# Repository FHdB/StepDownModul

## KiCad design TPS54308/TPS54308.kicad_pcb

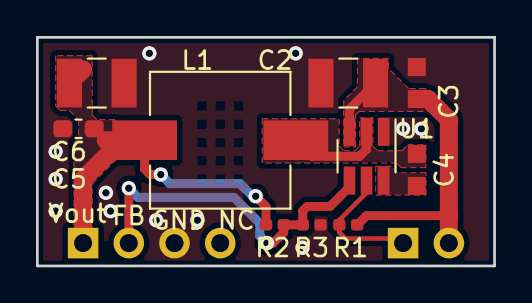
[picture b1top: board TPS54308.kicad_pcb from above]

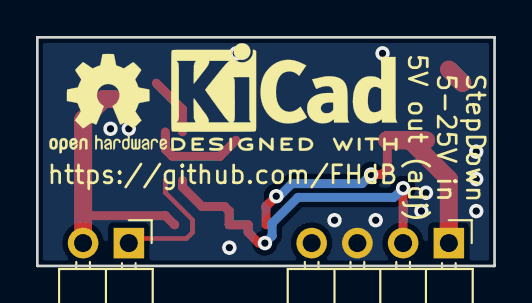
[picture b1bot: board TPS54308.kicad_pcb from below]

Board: 2 copper layers, 25.4 x 12.7 mm, 12 parts (2 on the bottom side), 7 nets.

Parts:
C2: 10u/50V/1210; C_1210_3225Metric_Pad1.39x2.70mm_HandSolder
C3, C4: 100n/50V/0603; C_0603_1608Metric_Pad0.99x1.00mm_HandSolder
C5: 100n/6.3V/0402; C_0603_1608Metric_Pad1.05x0.95mm_HandSolder
C6: 22u/6.3V/1210; C_1210_3225Metric_Pad1.39x2.70mm_HandSolder
L1: 74437346082_8u2_3.25A; L_Wuerth_WE-PD-Typ-M-Typ-S_Handsoldering
P1: CONN_01X02; PinHeader_1x02_P2.54mm_Horizontal
P2: CONN_01X04; PinHeader_1x04_P2.54mm_Horizontal
R1, R2: 100k/0402; R_0402_1005Metric_Handsolder
R3: 22k/0402; R_0402_1005Metric_Handsolder
U1: TPS54308DDC; SOT-23-6_Handsoldering

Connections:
BOOT: C4.1, U1.6
EN: P1.1, R1.2, U1.5
FB: P2.2, R2.2, R3.1, U1.4
GND: C2.2, C3.2, C5.2, C6.2, P2.3, R3.2, U1.1
SW: C4.2, L1.1, U1.2
VIN: C2.1, C3.1, P1.2, R1.1, U1.3
VOUT: C5.1, C6.1, L1.2, P2.1, R2.1

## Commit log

2018-06-12 placement draft
    drafted placement of all components and started routing.
2018-06-13 size reduction
    changed to 4pin pin headers, reduced board size, second placing attempt
2018-06-17 wired all connections
    ... additionally some copper fills and thermal vias
2018-07-12 Deleted aliases
2018-08-10 Silkscreen improvement
    Made references readable
2018-12-10 moved parts of silkscreen
2019-05-09 new pinout
    changed to a sideway standing pinout and rearranged components accordingly
2019-05-19 Ready for first test run
    Changed back to more compact coil
2019-05-22 finished routing
    ...but not yet satisfied as the gnd path between input and output capacitor is way too long.
2019-06-13 Ready for prototyping
